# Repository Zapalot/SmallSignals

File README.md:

# SmallSignals

This Repo contains:

- A brief summary of the workshop topics
- Kicad files for PCBs presented in the workshop 
- Some example programs used in the workshop

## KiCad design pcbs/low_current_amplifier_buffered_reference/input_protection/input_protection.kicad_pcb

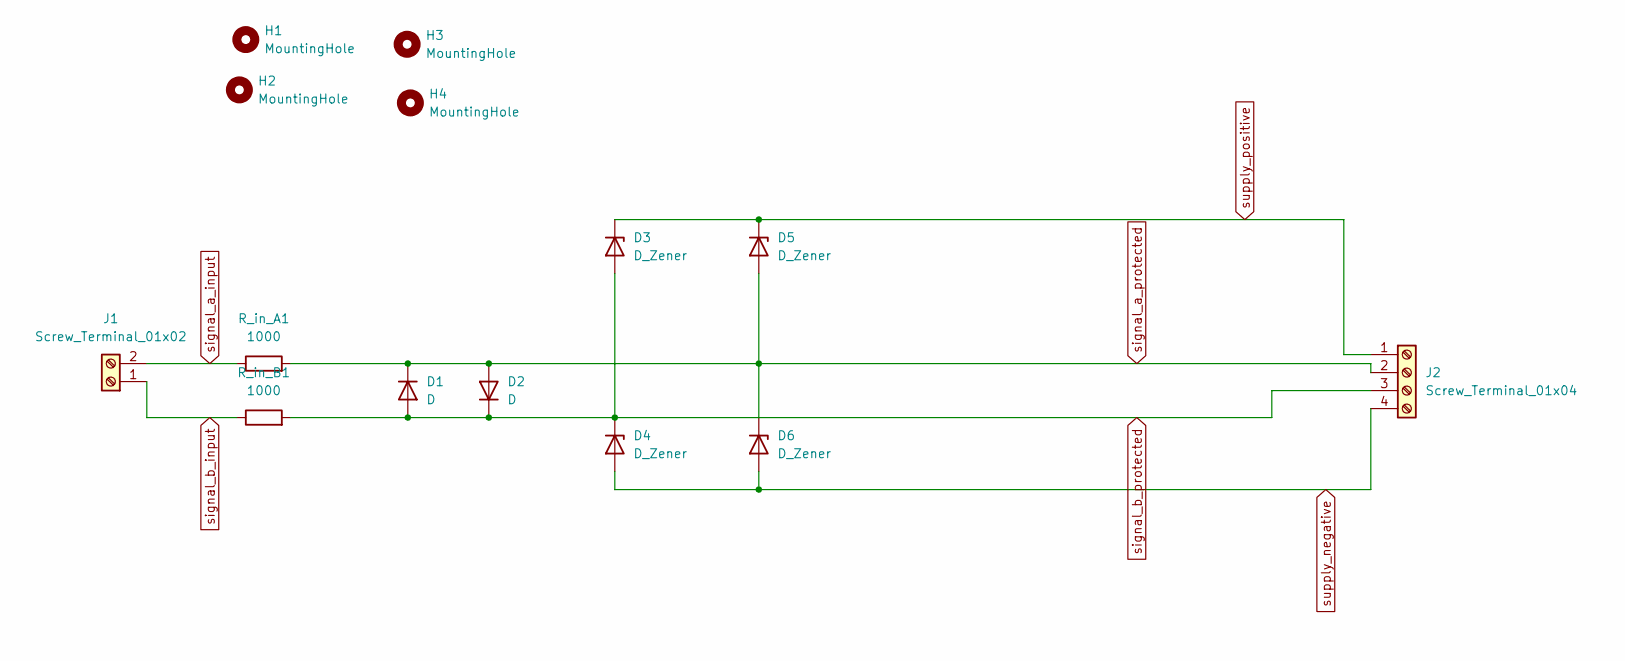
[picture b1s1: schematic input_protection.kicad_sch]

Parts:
D1, D2: D; D_DO-41_SOD81_P10.16mm_Horizontal
D3, D4, D5, D6: D_Zener; D_DO-41_SOD81_P10.16mm_Horizontal
H1, H2, H3, H4: MountingHole; MountingHole_3.2mm_M3_DIN965
J1: Screw_Terminal_01x02; TerminalBlock_MetzConnect_Type101_RT01602HBWC_1x02_P5.08mm_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
J2: Screw_Terminal_01x04; TerminalBlock_MetzConnect_Type101_RT01604HBWC_1x04_P5.08mm_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
R_in_A1: 1000; R_Axial_DIN0207_L6.3mm_D2.5mm_P10.16mm_Horizontal
R_in_B1: 1000; R_Axial_DIN0207_L6.3mm_D2.5mm_P10.16mm_Horizontal

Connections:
signal_a_input: J1.2, R_in_A1.1
signal_a_protected: D1.1 (K), D2.2 (A), D5.2 (A), D6.1 (K), J2.2, R_in_A1.2
signal_b_input: J1.1, R_in_B1.1
signal_b_protected: D1.2 (A), D2.1 (K), D3.2 (A), D4.1 (K), J2.3, R_in_B1.2
supply_negative: D4.2 (A), D6.2 (A), J2.4
supply_positive: D3.1 (K), D5.1 (K), J2.1

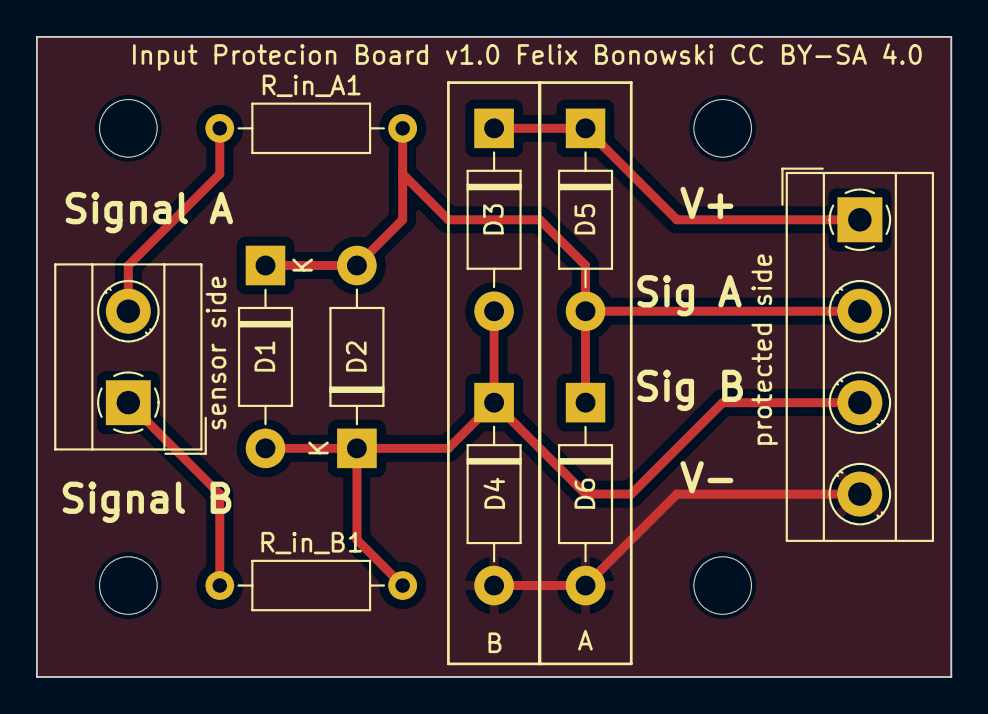
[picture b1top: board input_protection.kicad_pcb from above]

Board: 2 copper layers, 50.8 x 35.6 mm, 14 parts (0 on the bottom side), 6 nets.

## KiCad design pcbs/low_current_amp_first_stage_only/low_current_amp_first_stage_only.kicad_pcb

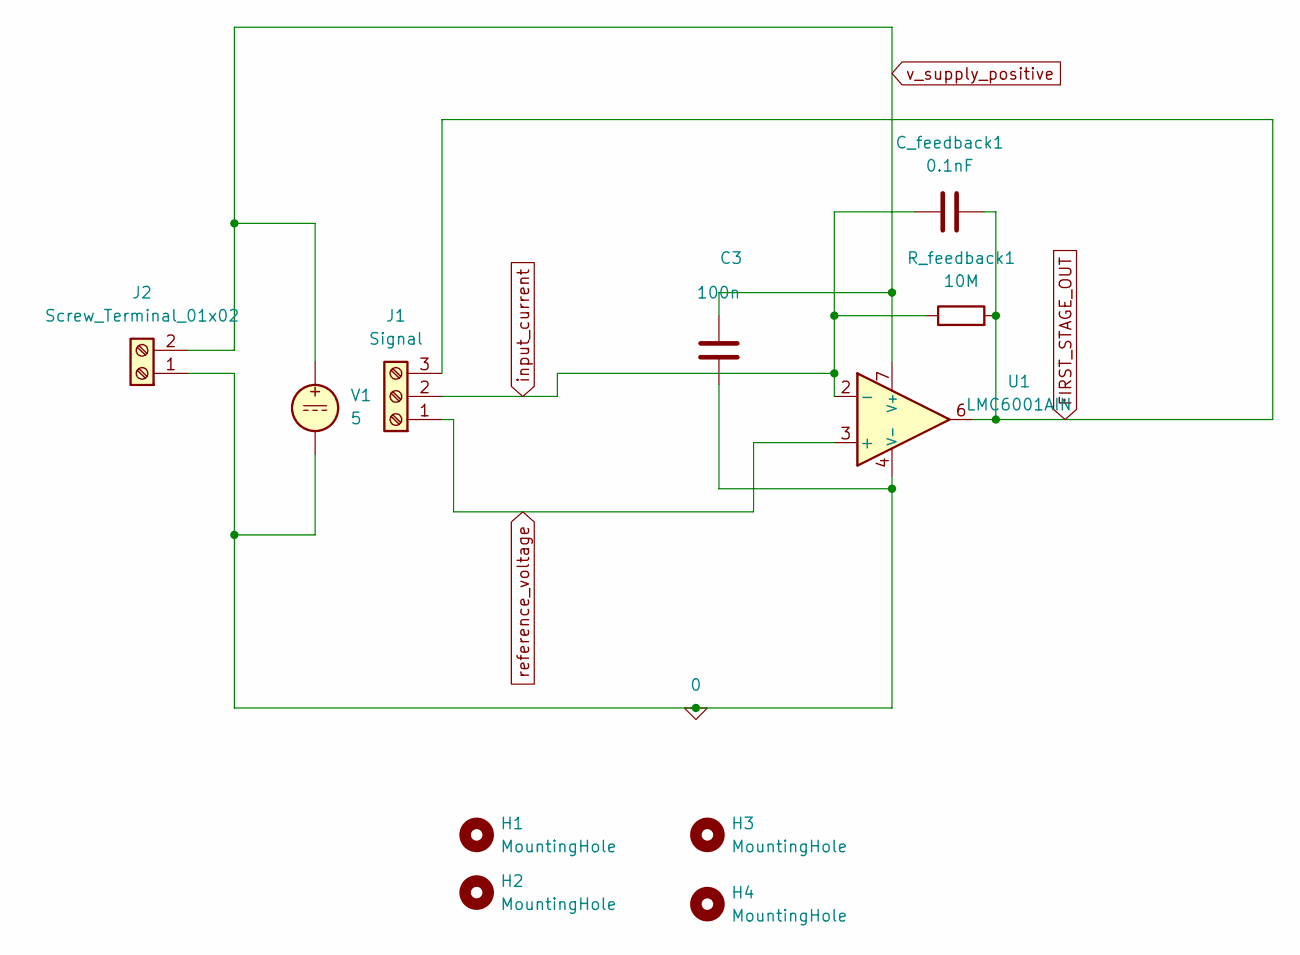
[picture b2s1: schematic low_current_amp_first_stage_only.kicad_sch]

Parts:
C3: 100n; C_Disc_D7.5mm_W2.5mm_P5.00mm
C_feedback1: 0.1nF; C_Rect_L13.0mm_W6.0mm_P10.00mm_FKS3_FKP3_MKS4
H1, H2, H3, H4: MountingHole; MountingHole_3.2mm_M3_DIN965
J1: Signal; TerminalBlock_MetzConnect_Type101_RT01603HBWC_1x03_P5.08mm_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
J2: Screw_Terminal_01x02; TerminalBlock_MetzConnect_Type101_RT01602HBWC_1x02_P5.08mm_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
R_feedback1: 10M; R_Axial_DIN0207_L6.3mm_D2.5mm_P10.16mm_Horizontal
U1: LMC6001AIN; DIP-8_W7.62mm_LongPads
V1: 5

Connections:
0: C3.2, J2.1, U1.4 (V-), V1.2
FIRST_STAGE_OUT: C_feedback1.2, J1.3, R_feedback1.2, U1.6
input_current: C_feedback1.1, J1.2, R_feedback1.1, U1.2 (-)
reference_voltage: J1.1, U1.3 (+)
v_supply_positive: C3.1, J2.2, U1.7 (V+), V1.1

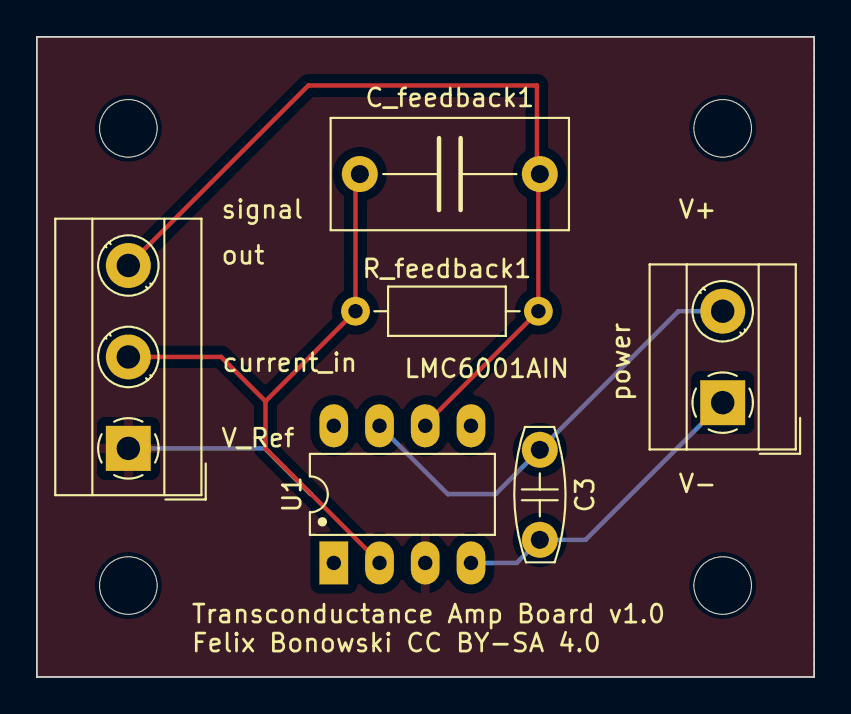
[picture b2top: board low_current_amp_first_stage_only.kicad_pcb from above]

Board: 2 copper layers, 43.2 x 35.6 mm, 10 parts (0 on the bottom side), 5 nets.

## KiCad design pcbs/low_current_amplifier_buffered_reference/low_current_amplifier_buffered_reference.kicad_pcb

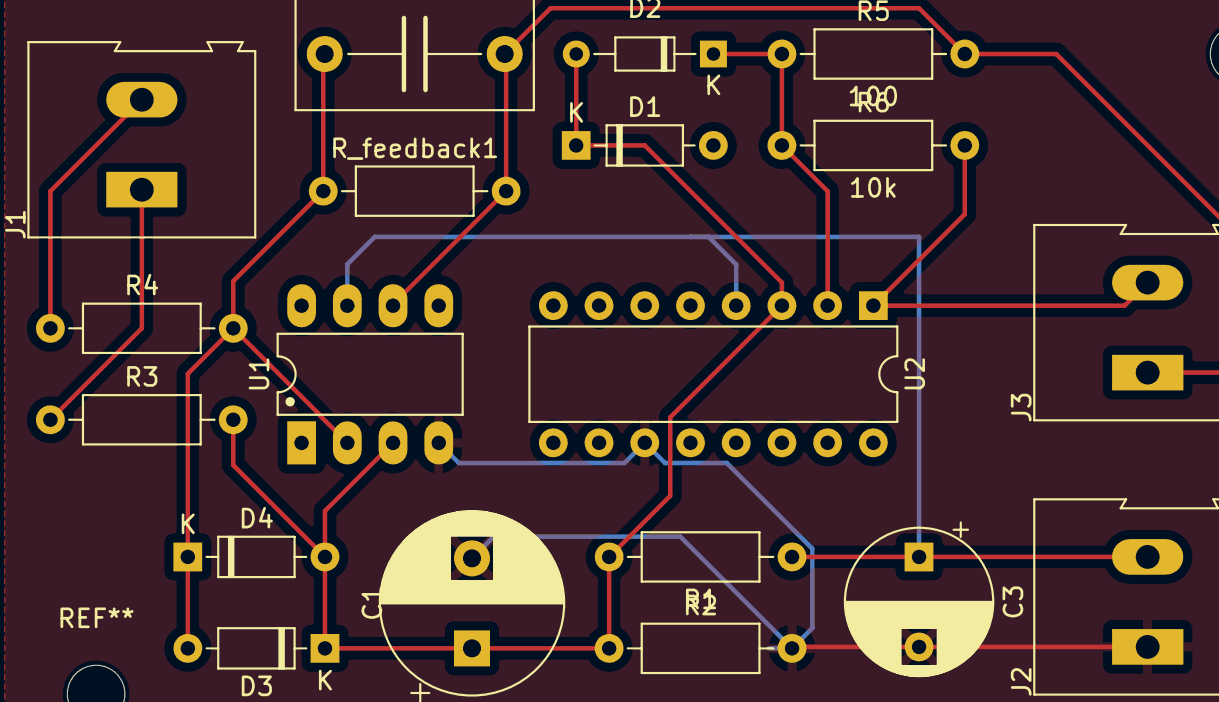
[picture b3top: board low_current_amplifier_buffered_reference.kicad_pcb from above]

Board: 2 copper layers, 19 parts (0 on the bottom side), 9 nets.

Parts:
C1: 100µF; CP_Radial_D10.0mm_P5.00mm
C2: 0.1nF; C_Rect_L13.0mm_W6.0mm_P10.00mm_FKS3_FKP3_MKS4
C3: 100µ; CP_Radial_D8.0mm_P5.00mm
D1, D3, D4: D; D_DO-35_SOD27_P7.62mm_Horizontal
D2: D; D_DO-34_SOD68_P7.62mm_Horizontal
J1: input; TerminalBlock_Altech_AK300-2_P5.00mm
J2: power_supply; TerminalBlock_Altech_AK300-2_P5.00mm
J3: output; TerminalBlock_Altech_AK300-2_P5.00mm
R1, R2, R5: 100; R_Axial_DIN0207_L6.3mm_D2.5mm_P10.16mm_Horizontal
R3, R4, R6: 10k; R_Axial_DIN0207_L6.3mm_D2.5mm_P10.16mm_Horizontal
R_feedback1: 10M; R_Axial_DIN0207_L6.3mm_D2.5mm_P10.16mm_Horizontal
U1: LMC6001AIN; DIP-8_W7.62mm_LongPads
U2: TS974ID; DIP-16_W7.62mm

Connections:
FIRST_STAGE_OUT: C2.2, J3.1, R5.2, R_feedback1.2, U1.6
unnamed: D1.2 (A), D2.1 (K), R5.1, R6.1, U2.2 (-)
unnamed: C2.1, D3.2 (A), D4.1 (K), R4.2, R_feedback1.1, U1.2 (-)
unnamed: J1.1, R3.1
V_Ref: C1.1, D1.1 (K), D2.2 (A), D3.1 (K), D4.2 (A), R1.2, R2.1, R3.2, U1.3 (+), U2.3 (+)
V_supply_negative: C1.2, C3.2, J2.1, R2.2, U1.4 (V-), U2.11 (V-)
input: J1.2, R4.1
second_stage_out: J3.2, R6.2, U2.1
v_supply_positive: C3.1, J2.2, R1.1, U1.7 (V+), U2.4 (V+)

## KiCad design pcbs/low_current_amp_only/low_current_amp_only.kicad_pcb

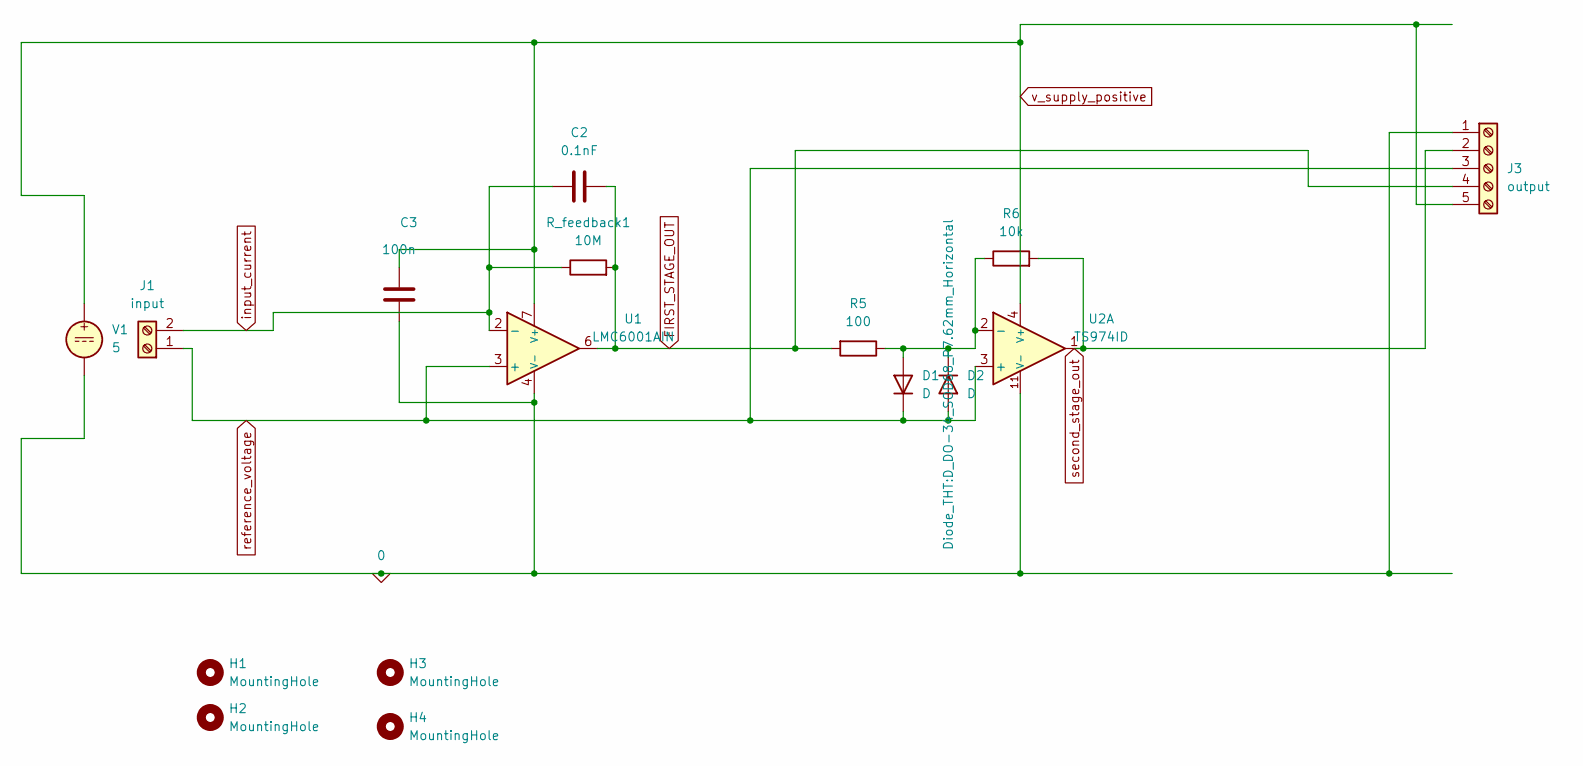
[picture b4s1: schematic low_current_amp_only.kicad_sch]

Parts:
C2: 0.1nF; C_Rect_L13.0mm_W6.0mm_P10.00mm_FKS3_FKP3_MKS4
C3: 100n; C_Disc_D7.5mm_W2.5mm_P5.00mm
D1: D; D_DO-41_SOD81_P7.62mm_Horizontal
D2: D; D_DO-34_SOD68_P7.62mm_Horizontal
H1, H2, H3, H4: MountingHole; MountingHole_3.2mm_M3_DIN965
J1: input; TerminalBlock_MetzConnect_Type101_RT01602HBWC_1x02_P5.08mm_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
J3: output; TerminalBlock_MetzConnect_Type101_RT01605HBWC_1x05_P5.08mm_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
R5: 100; R_Axial_DIN0207_L6.3mm_D2.5mm_P10.16mm_Horizontal
R6: 10k; R_Axial_DIN0207_L6.3mm_D2.5mm_P10.16mm_Horizontal
R_feedback1: 10M; R_Axial_DIN0207_L6.3mm_D2.5mm_P10.16mm_Horizontal
U1: LMC6001AIN; DIP-8_W7.62mm_LongPads
U2: TS974ID; DIP-16_W7.62mm
V1: 5

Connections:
0: C3.2, J3.1, U1.4 (V-), U2.11 (V-), V1.2
FIRST_STAGE_OUT: C2.2, J3.4, R5.2, R_feedback1.2, U1.6
unnamed: D1.2 (A), D2.1 (K), R5.1, R6.1, U2.2 (-)
input_current: C2.1, J1.2, R_feedback1.1, U1.2 (-)
reference_voltage: D1.1 (K), D2.2 (A), J1.1, J3.3, U1.3 (+), U2.3 (+)
second_stage_out: J3.2, R6.2, U2.1
v_supply_positive: C3.1, J3.5, U1.7 (V+), U2.4 (V+), V1.1

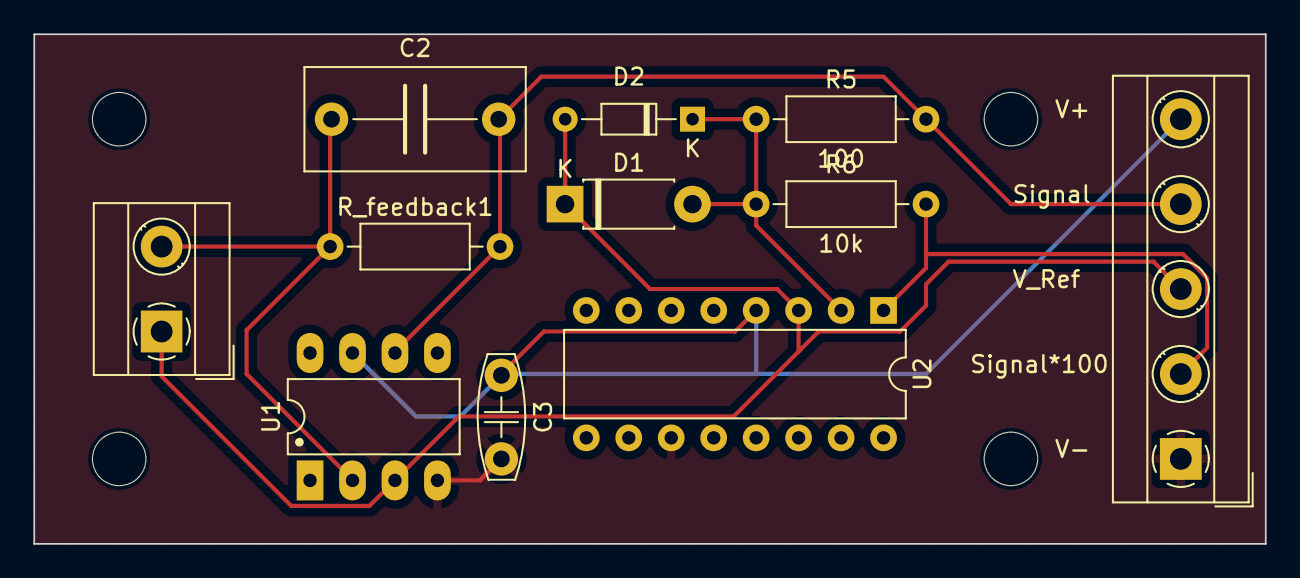
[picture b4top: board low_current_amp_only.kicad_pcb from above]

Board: 2 copper layers, 73.7 x 30.5 mm, 15 parts (0 on the bottom side), 7 nets.

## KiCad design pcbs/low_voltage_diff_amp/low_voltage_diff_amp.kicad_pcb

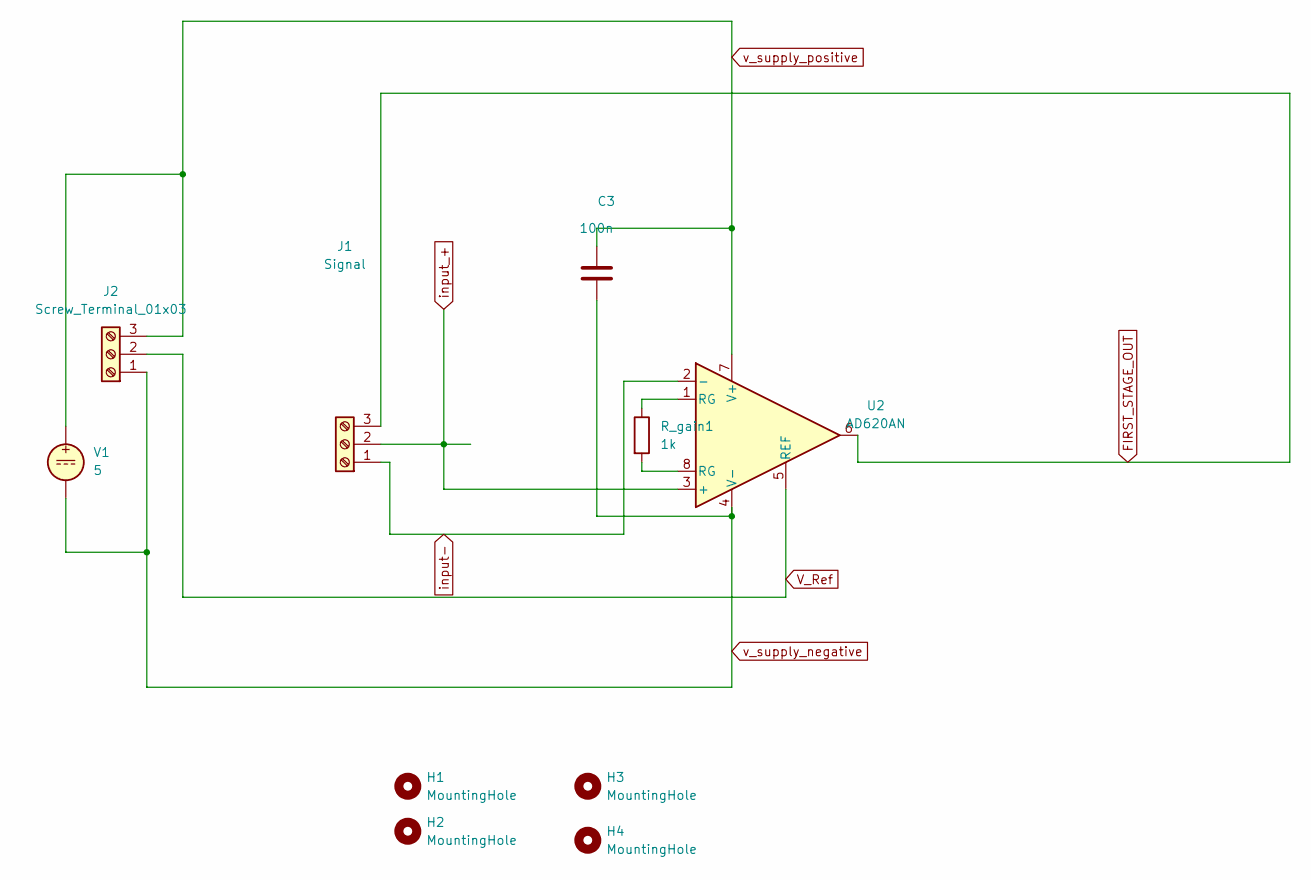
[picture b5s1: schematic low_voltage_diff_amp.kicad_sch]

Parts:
C3: 100n; C_Disc_D7.5mm_W2.5mm_P5.00mm
H1, H2, H3, H4: MountingHole; MountingHole_3.2mm_M3_DIN965
J1: Signal; TerminalBlock_MetzConnect_Type101_RT01603HBWC_1x03_P5.08mm_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
J2: Screw_Terminal_01x03; TerminalBlock_MetzConnect_Type101_RT01603HBWC_1x03_P5.08mm_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
R_gain1: 1k; R_Axial_DIN0207_L6.3mm_D2.5mm_P7.62mm_Horizontal
U2: AD620AN; DIP-8_W7.62mm_LongPads
V1: 5

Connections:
FIRST_STAGE_OUT: J1.3, U2.6
unnamed: R_gain1.1, U2.1 (RG)
unnamed: R_gain1.2, U2.8 (RG)
V_Ref: J2.2, U2.5 (REF)
input-: J1.1, U2.2 (-)
input_+: J1.2, U2.3 (+)
v_supply_negative: C3.2, J2.1, U2.4 (V-), V1.2
v_supply_positive: C3.1, J2.3, U2.7 (V+), V1.1

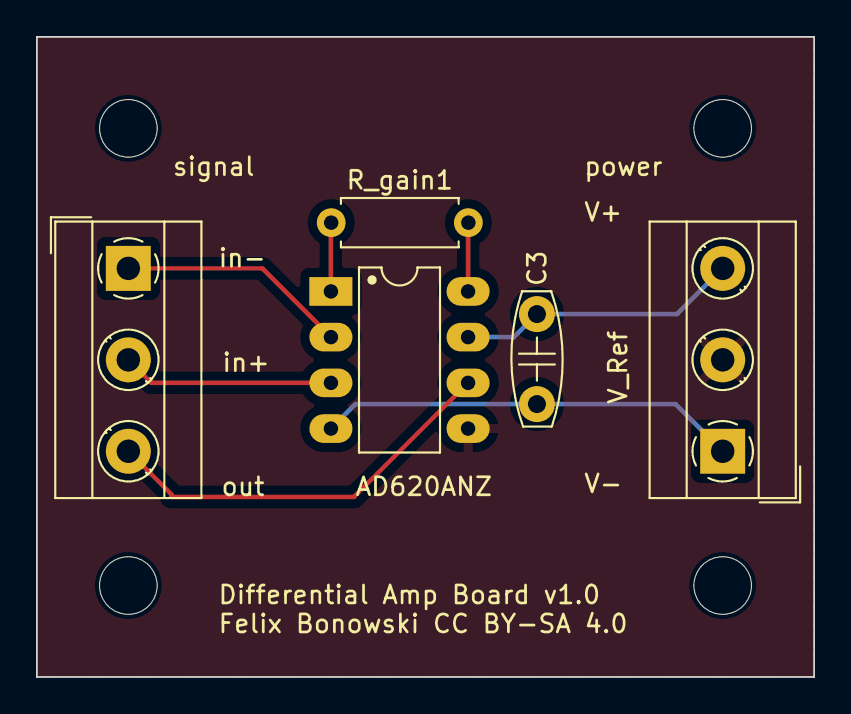
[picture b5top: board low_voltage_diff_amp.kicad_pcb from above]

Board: 2 copper layers, 43.2 x 35.6 mm, 9 parts (0 on the bottom side), 8 nets.

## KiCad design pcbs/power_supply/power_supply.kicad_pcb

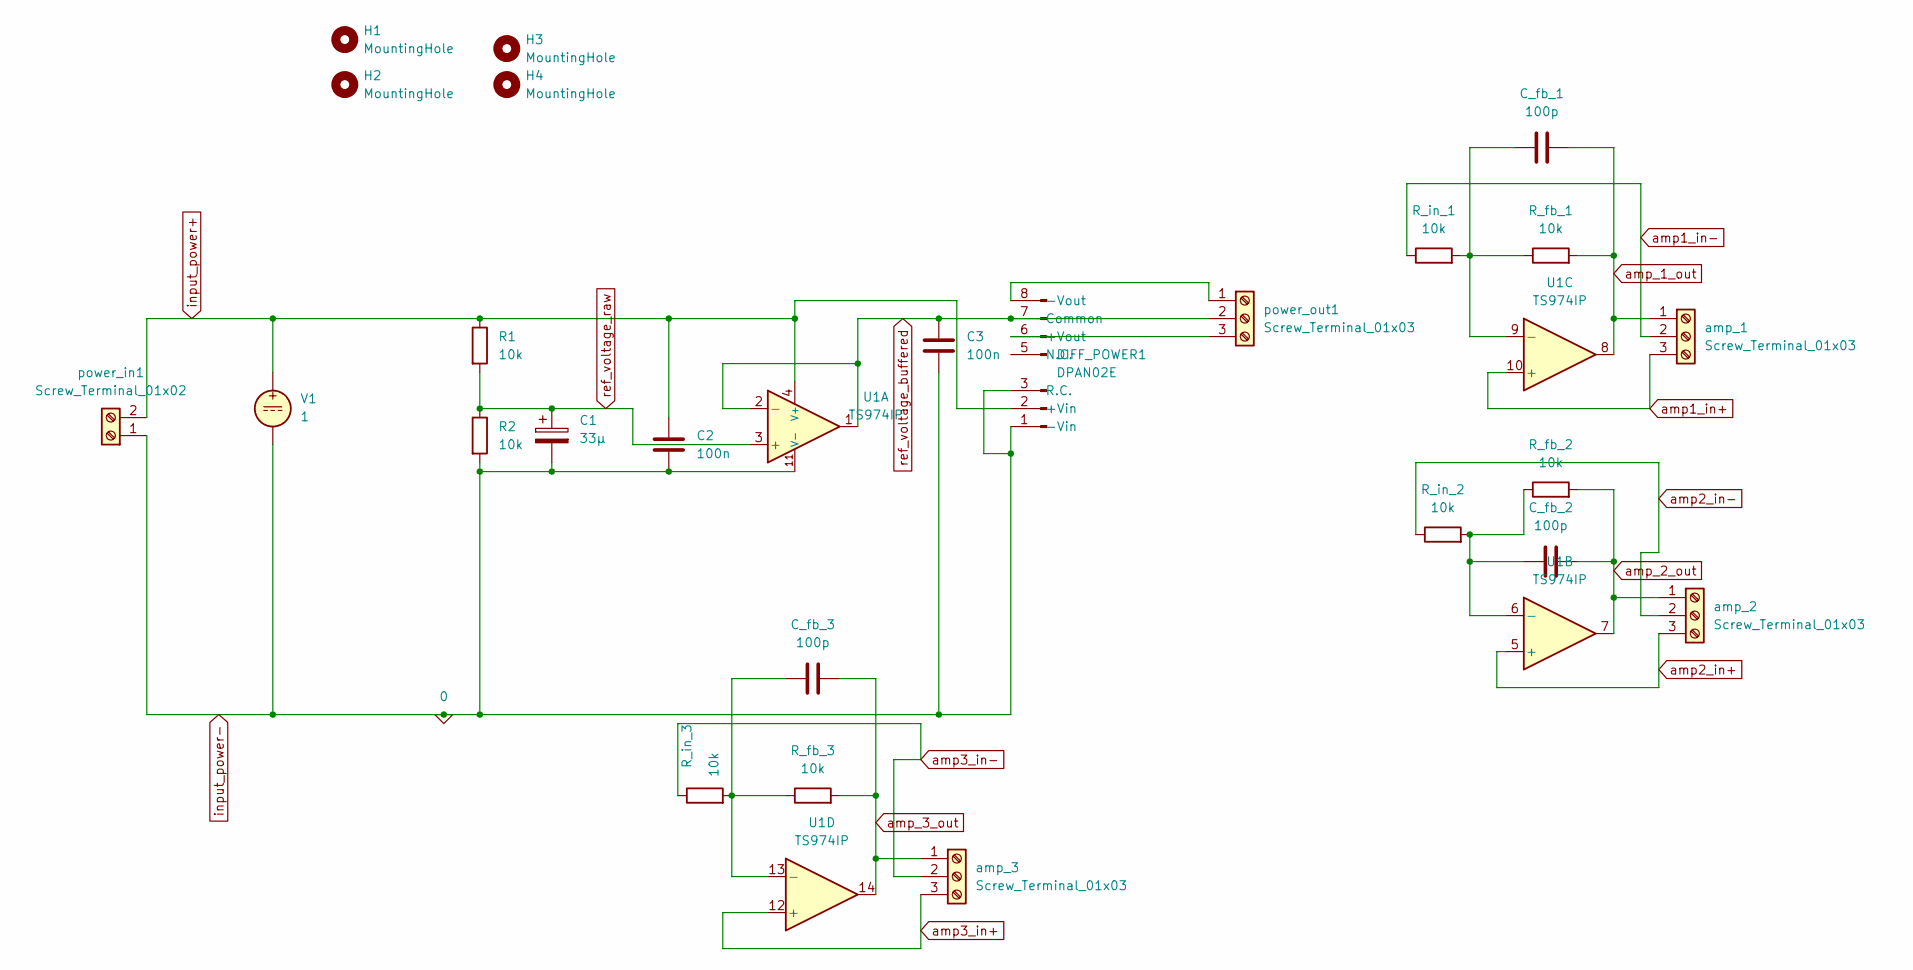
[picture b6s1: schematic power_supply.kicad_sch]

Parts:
C1: 33µ; CP_Radial_D5.0mm_P2.00mm
C2, C3: 100n; C_Disc_D5.0mm_W2.5mm_P2.50mm
C_fb_1, C_fb_2, C_fb_3: 100p; C_Disc_D5.0mm_W2.5mm_P5.00mm
DIFF_POWER1: DPAN02E; SIP-8_19x3mm_P2.54mm
H1, H2, H3, H4: MountingHole; MountingHole_3.2mm_M3_DIN965
R1, R2: 10k; R_Axial_DIN0207_L6.3mm_D2.5mm_P10.16mm_Horizontal
R_fb_1, R_fb_2, R_fb_3: 10k; R_Axial_DIN0207_L6.3mm_D2.5mm_P10.16mm_Horizontal
R_in_1, R_in_2, R_in_3: 10k; R_Axial_DIN0207_L6.3mm_D2.5mm_P10.16mm_Horizontal
U1: TS974IP; DIP-14_W7.62mm
V1: 1
amp_1, amp_2, amp_3: Screw_Terminal_01x03; TerminalBlock_MetzConnect_Type101_RT01603HBWC_1x03_P5.08mm_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
power_in1: Screw_Terminal_01x02; TerminalBlock_MetzConnect_Type101_RT01602HBWC_1x02_P5.08mm_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
power_out1: Screw_Terminal_01x03; TerminalBlock_MetzConnect_Type101_RT01603HBWC_1x03_P5.08mm_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

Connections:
unnamed: DIFF_POWER1.6 (+Vout), power_out1.3
unnamed: DIFF_POWER1.8 (-Vout), power_out1.1
unnamed: C_fb_2.1, R_fb_2.1, R_in_2.2, U1.6 (-)
unnamed: C_fb_1.1, R_fb_1.1, R_in_1.2, U1.9 (-)
unnamed: C_fb_3.1, R_fb_3.1, R_in_3.2, U1.13 (-)
amp1_in+: U1.10 (+), amp_1.3
amp1_in-: R_in_1.1, amp_1.2
amp2_in+: U1.5 (+), amp_2.3
amp2_in-: R_in_2.1, amp_2.2
amp3_in+: U1.12 (+), amp_3.3
amp3_in-: R_in_3.1, amp_3.2
amp_1_out: C_fb_1.2, R_fb_1.2, U1.8, amp_1.1
amp_2_out: C_fb_2.2, R_fb_2.2, U1.7, amp_2.1
amp_3_out: C_fb_3.2, R_fb_3.2, U1.14, amp_3.1
input_power+: C2.1, DIFF_POWER1.2 (+Vin), R1.1, U1.4 (V+), V1.1, power_in1.2
input_power-: C1.2, C2.2, C3.2, DIFF_POWER1.1 (-Vin), DIFF_POWER1.3 (R.C.), R2.2, U1.11 (V-), V1.2, power_in1.1
ref_voltage_buffered: C3.1, DIFF_POWER1.7 (Common), U1.1, U1.2 (-), power_out1.2
ref_voltage_raw: C1.1, R1.2, R2.1, U1.3 (+)

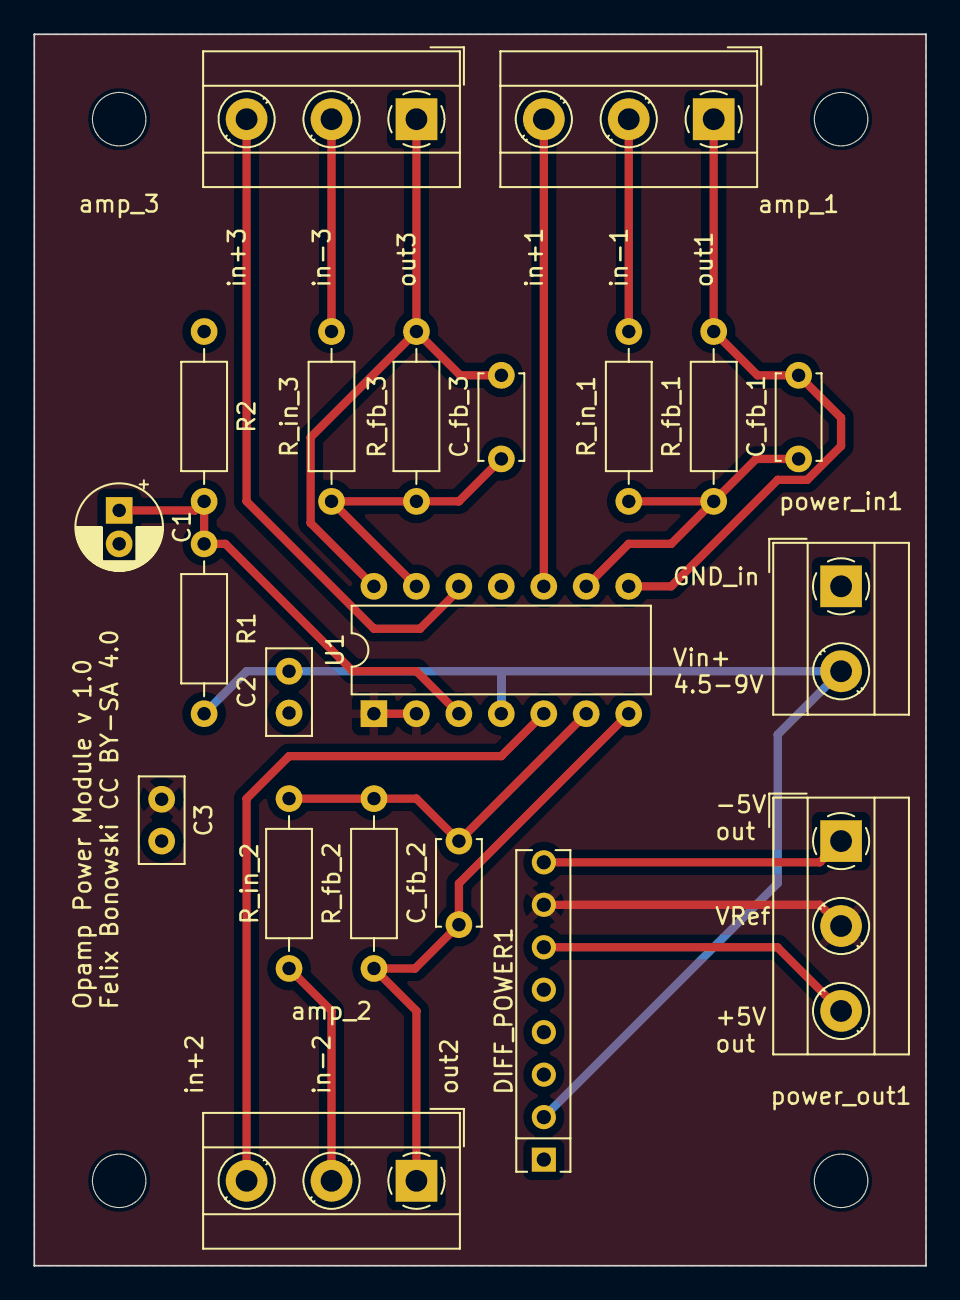
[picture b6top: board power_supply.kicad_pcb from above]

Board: 2 copper layers, 53.3 x 73.7 mm, 25 parts (0 on the bottom side), 18 nets.

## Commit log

2024-05-15 initial commit of pcbs
2024-05-15 first commit with cleaned up pcbs
2024-05-16 added workshop summary

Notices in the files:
pcbs/low_current_amp_first_stage_only/low_current_amp_first_stage_only.kicad_pcb:
Felix Bonowski CC BY-SA 4.0
pcbs/low_current_amplifier_buffered_reference/input_protection/input_protection.kicad_pcb:
Input Protecion Board v1.0 Felix Bonowski CC BY-SA 4.0
